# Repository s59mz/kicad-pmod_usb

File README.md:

# kicad-pmod_usb
PMOD PCB module for FPGA USB device implementation

An FPGA-based USB full-speed device core to implement USB-serial, USB-camera, USB-audio, USB-hid, etc.

It requires only 3 FPGA common IOs rather than additional chips.

RTL code available at:
https://github.com/s59mz/FPGA-USB-Device

Schematic:
[kicad-pmod_usb.pdf](kicad-pmod_usb.pdf)

BOM:
[kicad-pmod_usb.csv](kicad-pmod_usb.csv)

Gerbers:
[gerbers.zip](https://github.com/s59mz/kicad-pmod_usb/raw/main/gerbers.zip)

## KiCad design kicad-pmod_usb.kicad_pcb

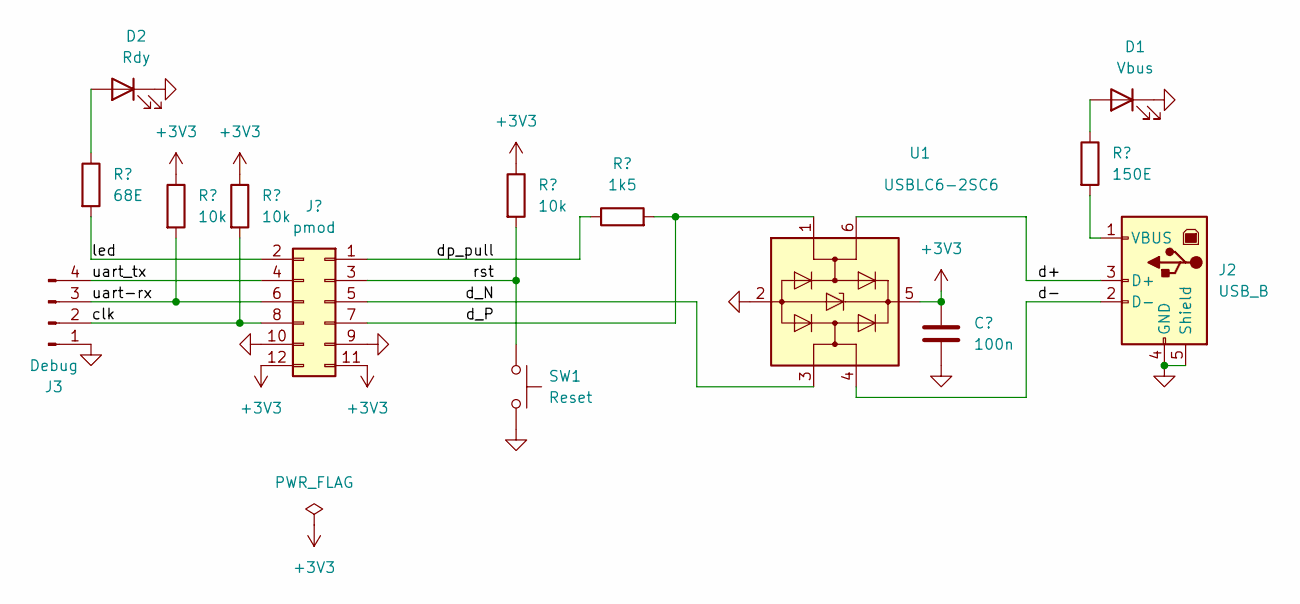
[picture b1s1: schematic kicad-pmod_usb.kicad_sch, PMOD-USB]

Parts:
C1: 100n; C_0603_1608Metric_Pad1.08x0.95mm_HandSolder
D1: Vbus; LED_0603_1608Metric_Pad1.05x0.95mm_HandSolder
D2: Rdy; LED_0603_1608Metric_Pad1.05x0.95mm_HandSolder
J1: pmod; PinHeader_2x06_P2.54mm_Horizontal
J2: USB_B; USB_B_Lumberg_2411_02_Horizontal
J3: Debug; PinHeader_1x04_P2.54mm_Vertical
R1: 1k5; R_0603_1608Metric_Pad0.98x0.95mm_HandSolder
R2: 68E; R_0603_1608Metric_Pad0.98x0.95mm_HandSolder
R3: 150E; R_0603_1608Metric_Pad0.98x0.95mm_HandSolder
R4, R5, R6: 10k; R_0603_1608Metric_Pad0.98x0.95mm_HandSolder
SW1: Reset; SW_SPST_FSMSM
U1: USBLC6-2SC6; SOT-23-6

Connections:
+3V3: C1.1, J1.11, J1.12, R4.1, R5.1, R6.1, U1.5 (VBUS)
/clk: J1.8, J3.2, R5.2
/d+: J2.3 (D+), U1.6 (I/O1)
/d-: J2.2 (D-), U1.4 (I/O2)
/d_N: J1.5, U1.3 (I/O2)
/d_P: J1.7, R1.2, U1.1 (I/O1)
/dp_pull: J1.1, R1.1
/led: J1.2, R2.2
/rst: J1.3, R4.2, SW1.1
/uart-rx: J1.6, J3.3, R6.2
/uart_tx: J1.4, J3.4
GND: C1.2, D1.1 (K), D2.1 (K), J1.9, J1.10, J2.4 (GND), J2.5 (Shield), J3.1, SW1.2, U1.2 (GND)
unnamed: D1.2 (A), R3.1
unnamed: D2.2 (A), R2.1
unnamed: J2.1 (VBUS), R3.2

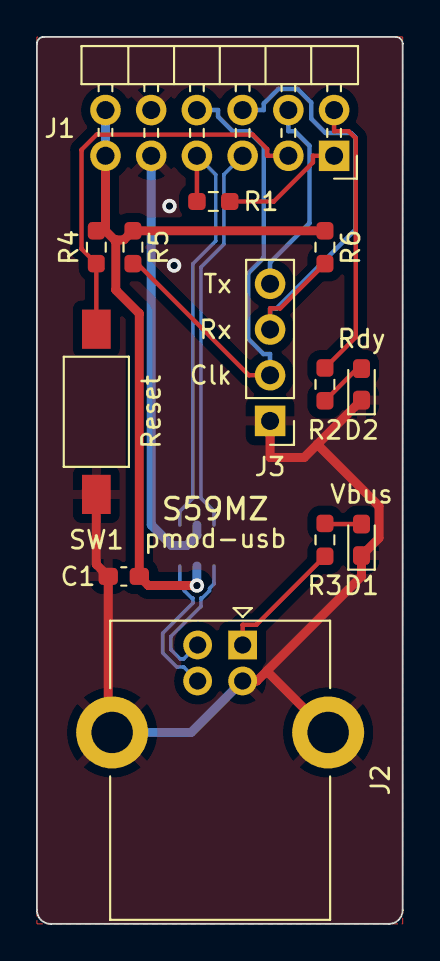
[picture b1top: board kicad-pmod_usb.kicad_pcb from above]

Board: 2 copper layers, 20.3 x 49.3 mm, 14 parts (1 on the bottom side), 15 nets.

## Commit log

2023-12-16 change resistor values
2023-12-17 rename
